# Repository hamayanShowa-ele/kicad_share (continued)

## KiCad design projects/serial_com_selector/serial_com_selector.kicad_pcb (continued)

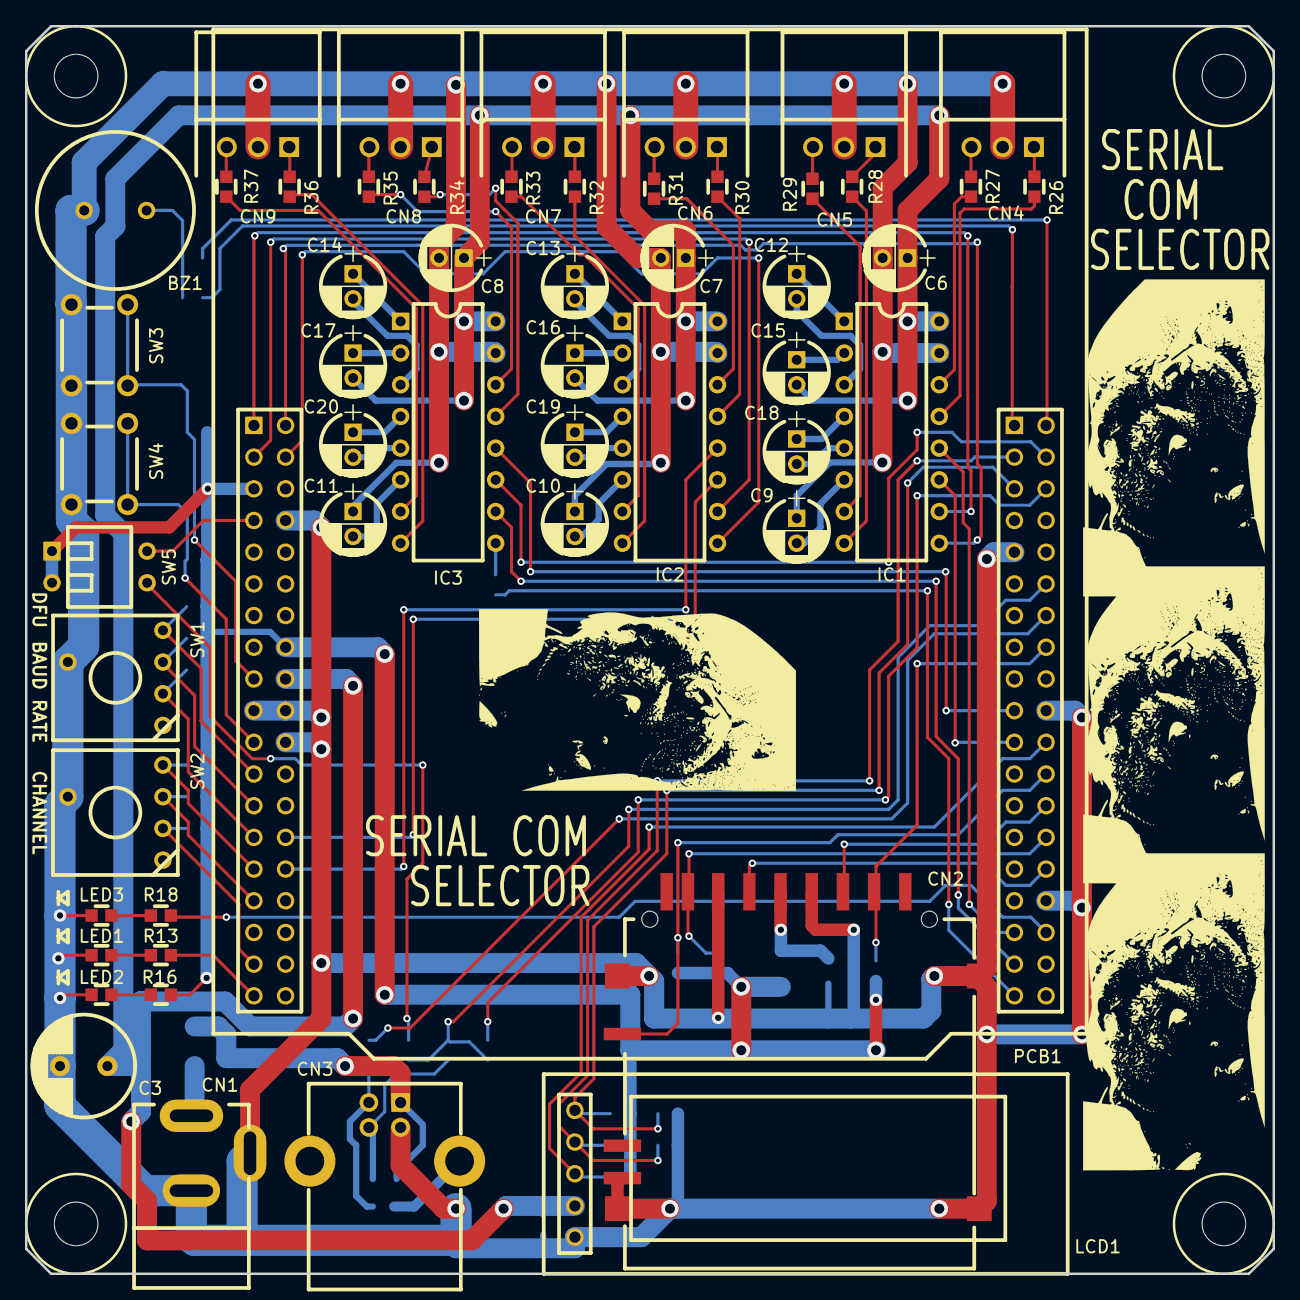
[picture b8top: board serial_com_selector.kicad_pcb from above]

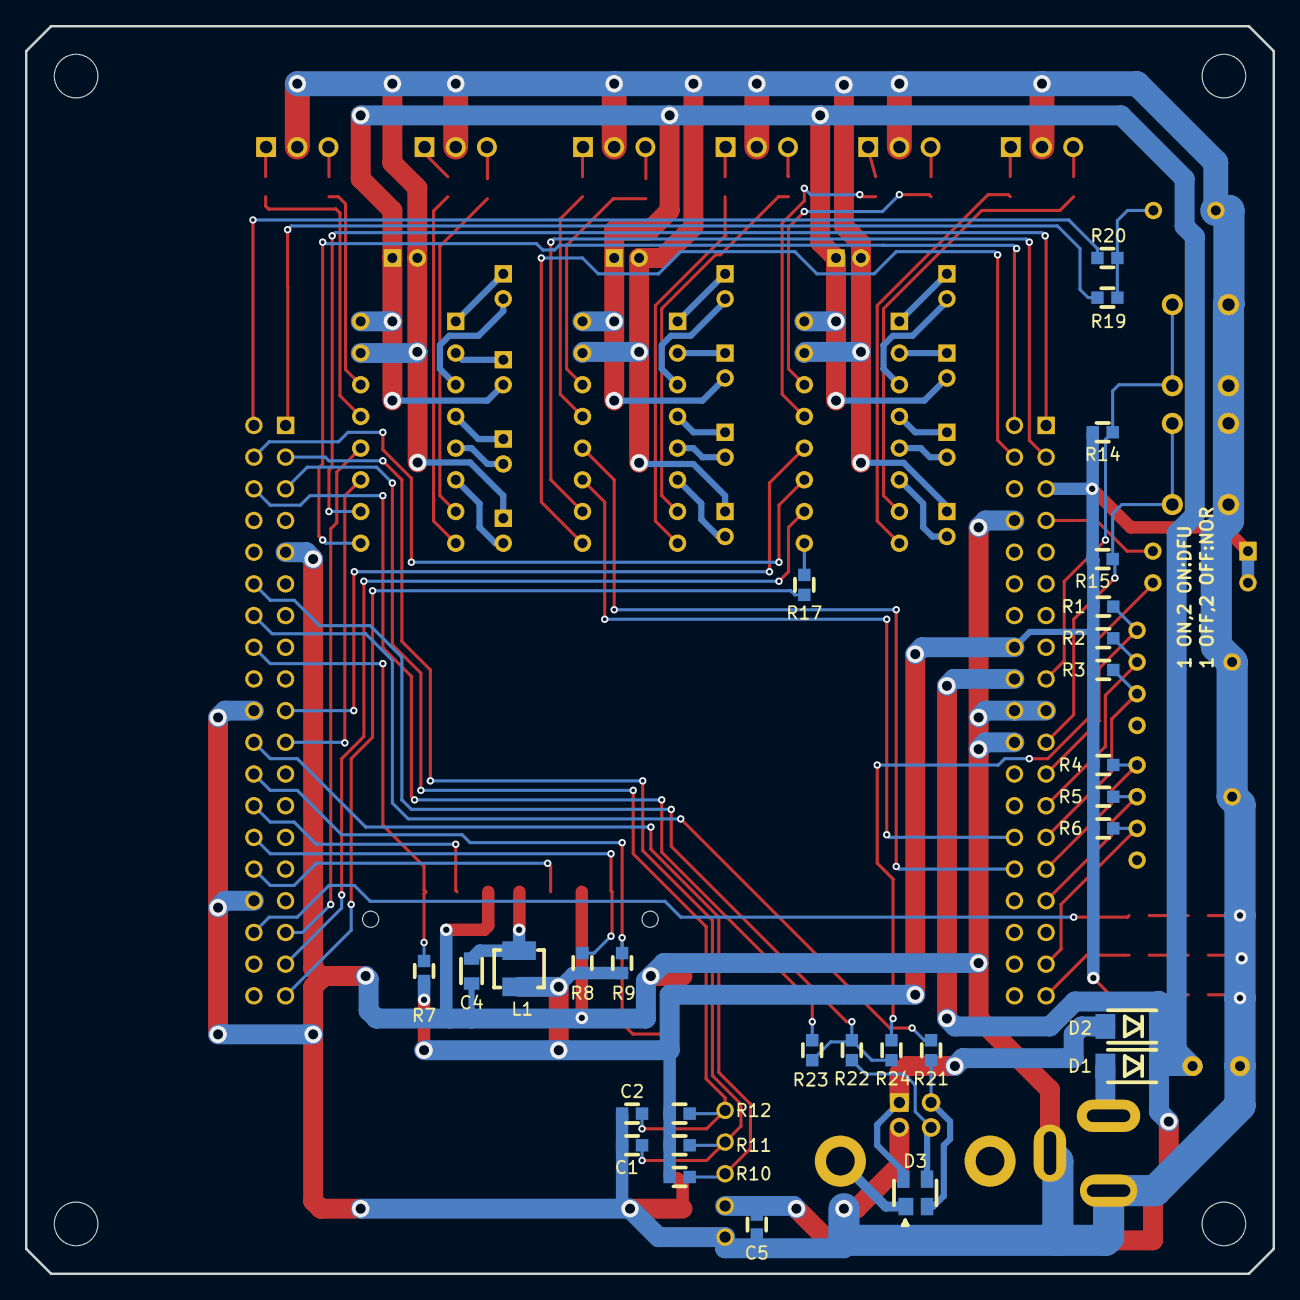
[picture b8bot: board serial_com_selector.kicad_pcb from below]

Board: 2 copper layers, 100.0 x 100.0 mm, 83 parts (29 on the bottom side), 93 nets.

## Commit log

2021-05-28 create any symbols.
2021-05-30 Strawberry-linux製のセンサーモジュール基板のシンボルお追加。
2021-06-01 Matrix LED基板の追加。
2021-06-01 Matrix LED control基板の追加
2021-06-01 ESP32開発基板の追加。
2021-06-01 赤外線送受信回路の追加。
2021-06-24 シンボルを、カテゴリー毎にマージした。
2021-06-24 フットプリントを、カテゴリー毎にマージした。
2021-06-24 2102基板 DIO-0808 F1バージョンのプロジェクトを追加。
2021-06-29 HIF3FC-30PA-2.54DSのfootprintの追加。
2021-06-29 74シリーズのシンボルにオリジナルのシンボルを追加。
2021-06-29 .gitignoreファイルの更新と、部品表の追加。
2021-08-19 スピーカーのライブラリを追加した。
2021-08-19 Low Threshold Short Checkerのプロジェクトを追加した。
2021-08-19 R2の追加。
2021-12-06 ライブラリの追加。
2021-12-06 シンボルの追加。
2021-12-06 新規プロジェクトの追加。
2021-12-08 基板端に電源コネクタを追加。
2021-12-10 ロン君の署名を追加。
2022-01-27 Add a project for Media Converter.
2022-02-18 Update and add to the parts library.
2022-02-18 Added a probe conversion board for logic analyzers.
2022-03-23 A device that uses NUCLEO-F446RE to connect one USB serial to up to six serials. It can also be used as a serial/Ethernet converter by using the Ethernet shield.
2022-06-21 Analog Discovery2 conversion board. However, the signal line names on the silk are upside down and wrong.
2022-07-04 Addition of UNIT DISPLAY board.
2022-07-05 Added 0231C board project.
2022-07-05 Added board-to-board wiring diagram.
2022-07-05 Added a project for 2204 boards.
2022-09-26 Added a project for 2209 boards.
2022-11-09 Added projects for boards 2212 and 2213.
